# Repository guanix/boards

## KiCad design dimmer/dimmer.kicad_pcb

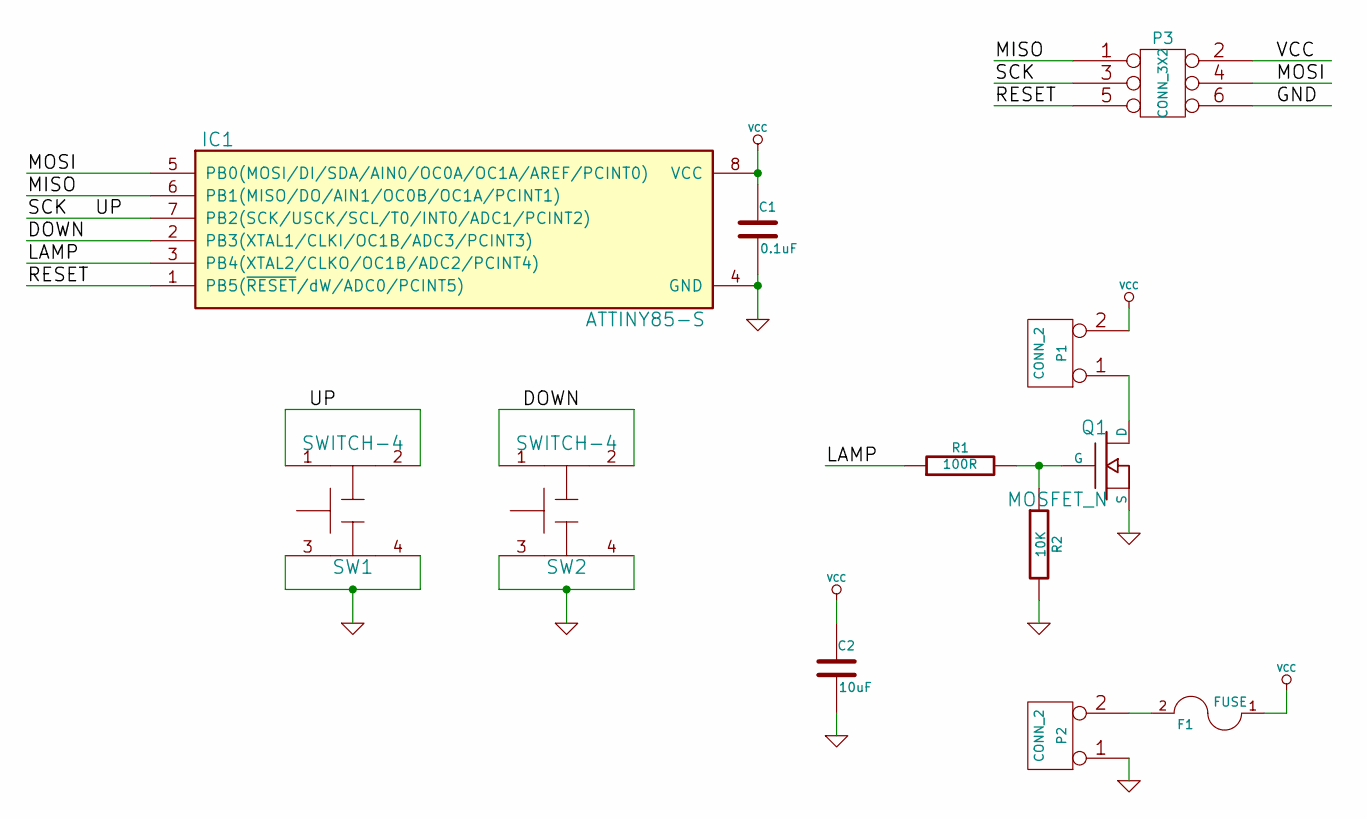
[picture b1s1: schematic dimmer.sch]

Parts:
C1: 0.1uF
C2: 10uF
F1: FUSE
IC1: ATTINY85-S; SO8-200
P1, P2: CONN_2
P3: CONN_3X2
Q1: MOSFET_N
R1: 100R
R2: 10K
SW1, SW2: SWITCH-4

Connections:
/DOWN: IC1.2 (PB3(XTAL1/CLKI/OC1B/ADC3/PCINT3)), SW2.1, SW2.2
/LAMP: IC1.3 (PB4(XTAL2/CLKO/OC1B/ADC2/PCINT4)), R1.1
/MISO: IC1.6 (PB1(MISO/DO/AIN1/OC0B/OC1A/PCINT1)), P3.1
/MOSI: IC1.5 (PB0(MOSI/DI/SDA/AIN0/OC0A/OC1A/AREF/PCI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), P3.4
/RESET: IC1.1 (PB5(~RESET~/dW/ADC0/PCINT5)), P3.5
/SCK: IC1.7 (PB2(SCK/USCK/SCL/T0/INT0/ADC1/PCINT2)), P3.3, SW1.1, SW1.2
GND: C1.2, C2.2, IC1.4 (GND), P2.1, P3.6, Q1.S, R2.2, SW1.3, SW1.4, SW2.3, SW2.4
unnamed: F1.2, P2.2 (PM)
unnamed: P1.1, Q1.D
unnamed: Q1.G, R1.2, R2.1
VCC: C1.1, C2.1, F1.1, IC1.8 (VCC), P1.2 (PM), P3.2

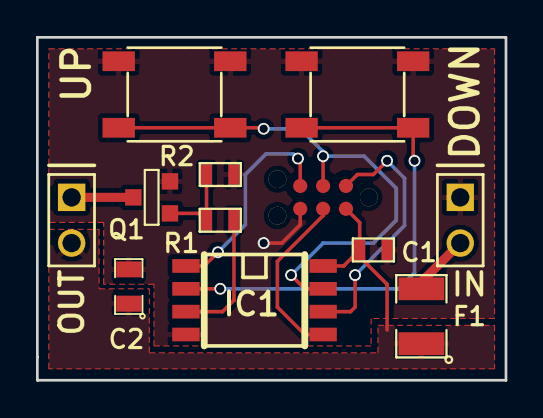
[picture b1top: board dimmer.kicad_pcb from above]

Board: 2 copper layers, 26.0 x 19.0 mm, 12 parts (0 on the bottom side), 11 nets.

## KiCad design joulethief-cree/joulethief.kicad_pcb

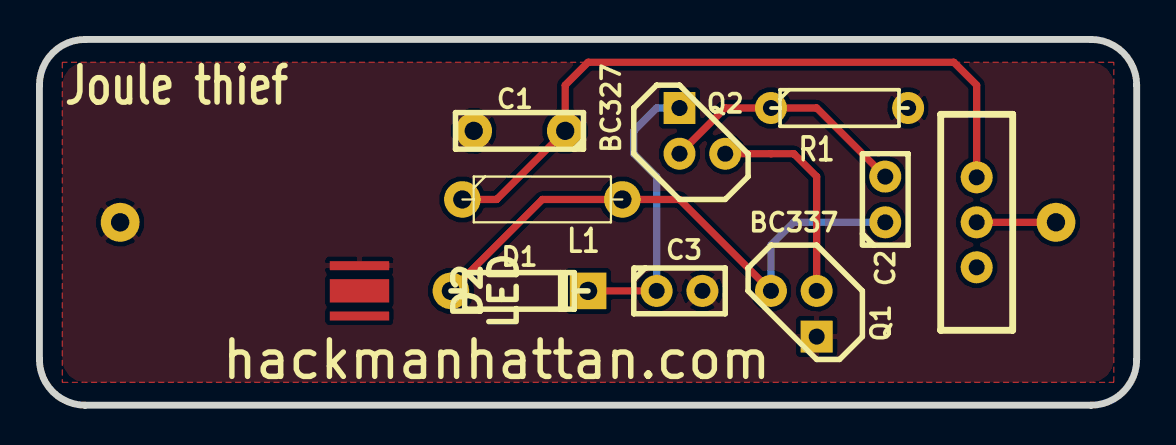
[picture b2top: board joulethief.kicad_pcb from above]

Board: 2 copper layers, 61.0 x 20.3 mm, 11 parts (1 on the bottom side), 7 nets.

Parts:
BT1: BATTERY; BATTERY-AA
C1: 10uF; C2
C2: 150pF; C1
C3: 100nF; C1
D1: 1N4148; D3
D2: LED; CREE-XPC-LED
L1: 22uH; R3-5
Q1: BC337; TO92
Q2: BC327; TO92
R1: 100K; R3
SW1: SWITCH_INV; SWITCH-SPDT-EG1218

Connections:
GND: BT1.2, C1.2, C3.2, D2.2, Q1.1, R1.2
unnamed: BT1.1, SW1.2
unnamed: C2.1, D1.1, D2.1, L1.2, Q1.3
unnamed: Q1.2, Q2.3
unnamed: C1.1, L1.1, SW1.3
unnamed: C3.1, D1.2, Q2.1
unnamed: C2.2, Q2.2, R1.1

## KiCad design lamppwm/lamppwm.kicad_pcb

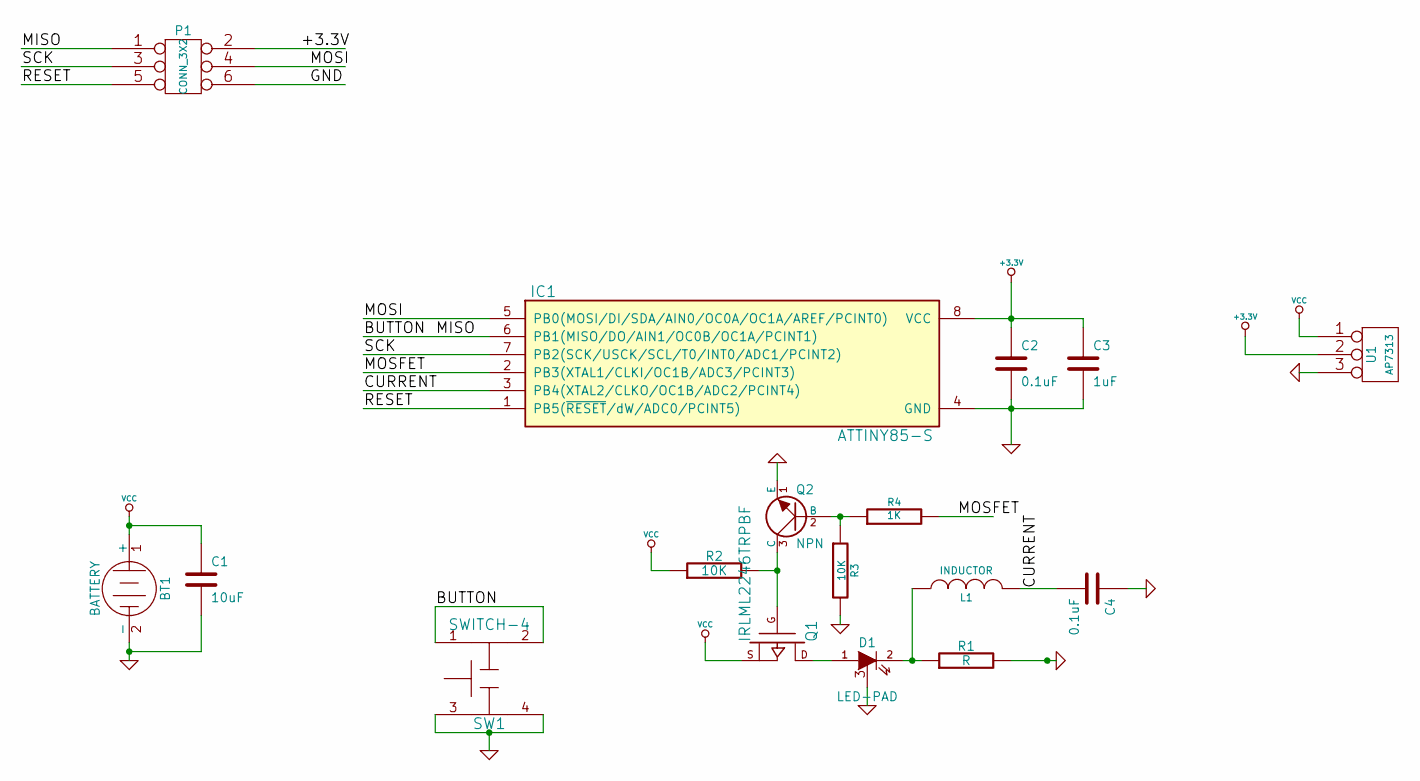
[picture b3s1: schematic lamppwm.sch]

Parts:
BT1: BATTERY
C1: 10uF
C2, C4: 0.1uF
C3: 1uF
D1: LED-PAD
IC1: ATTINY85-S; SO8-200
L1: INDUCTOR
P1: CONN_3X2
Q1: IRLML2246TRPBF
Q2: NPN
R1: R
R2: 10K
R3: 10K
R4: 1K
SW1: SWITCH-4
U1: AP7313

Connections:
+3.3V: C2.1, C3.1, IC1.8 (VCC), P1.2, U1.2 (PM)
/BUTTON: IC1.6 (PB1(MISO/DO/AIN1/OC0B/OC1A/PCINT1)), P1.1, SW1.1, SW1.2
/CURRENT: C4.2, IC1.3 (PB4(XTAL2/CLKO/OC1B/ADC2/PCINT4)), L1.2
/MOSFET: IC1.2 (PB3(XTAL1/CLKI/OC1B/ADC3/PCINT3)), R4.2
/MOSI: IC1.5 (PB0(MOSI/DI/SDA/AIN0/OC0A/OC1A/AREF/PCI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), P1.4
/RESET: IC1.1 (PB5(~RESET~/dW/ADC0/PCINT5)), P1.5
/SCK: IC1.7 (PB2(SCK/USCK/SCL/T0/INT0/ADC1/PCINT2)), P1.3
GND: BT1.2 (-), C1.2, C2.2, C3.2, C4.1, D1.3 (PAD), IC1.4 (GND), P1.6, Q2.1 (E), R1.2, R3.2, SW1.3, SW1.4, U1.3
unnamed: D1.1 (A), Q1.D
unnamed: Q2.2 (B), R3.1, R4.1
unnamed: Q1.G, Q2.3 (C), R2.2
unnamed: D1.2 (K), L1.1, R1.1
VCC: BT1.1 (+), C1.1, Q1.S, R2.1, U1.1

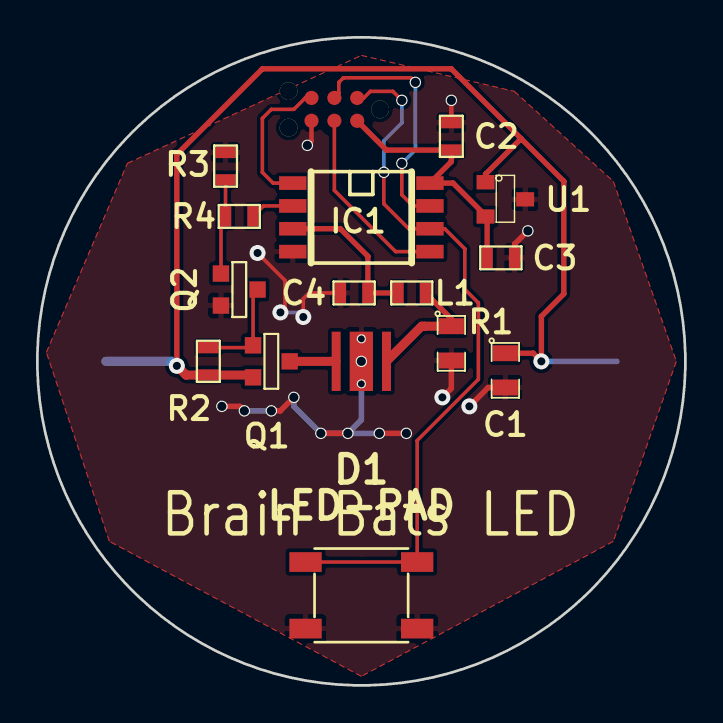
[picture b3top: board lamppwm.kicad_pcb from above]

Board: 2 copper layers, 36.0 x 36.0 mm, 17 parts (1 on the bottom side), 13 nets.

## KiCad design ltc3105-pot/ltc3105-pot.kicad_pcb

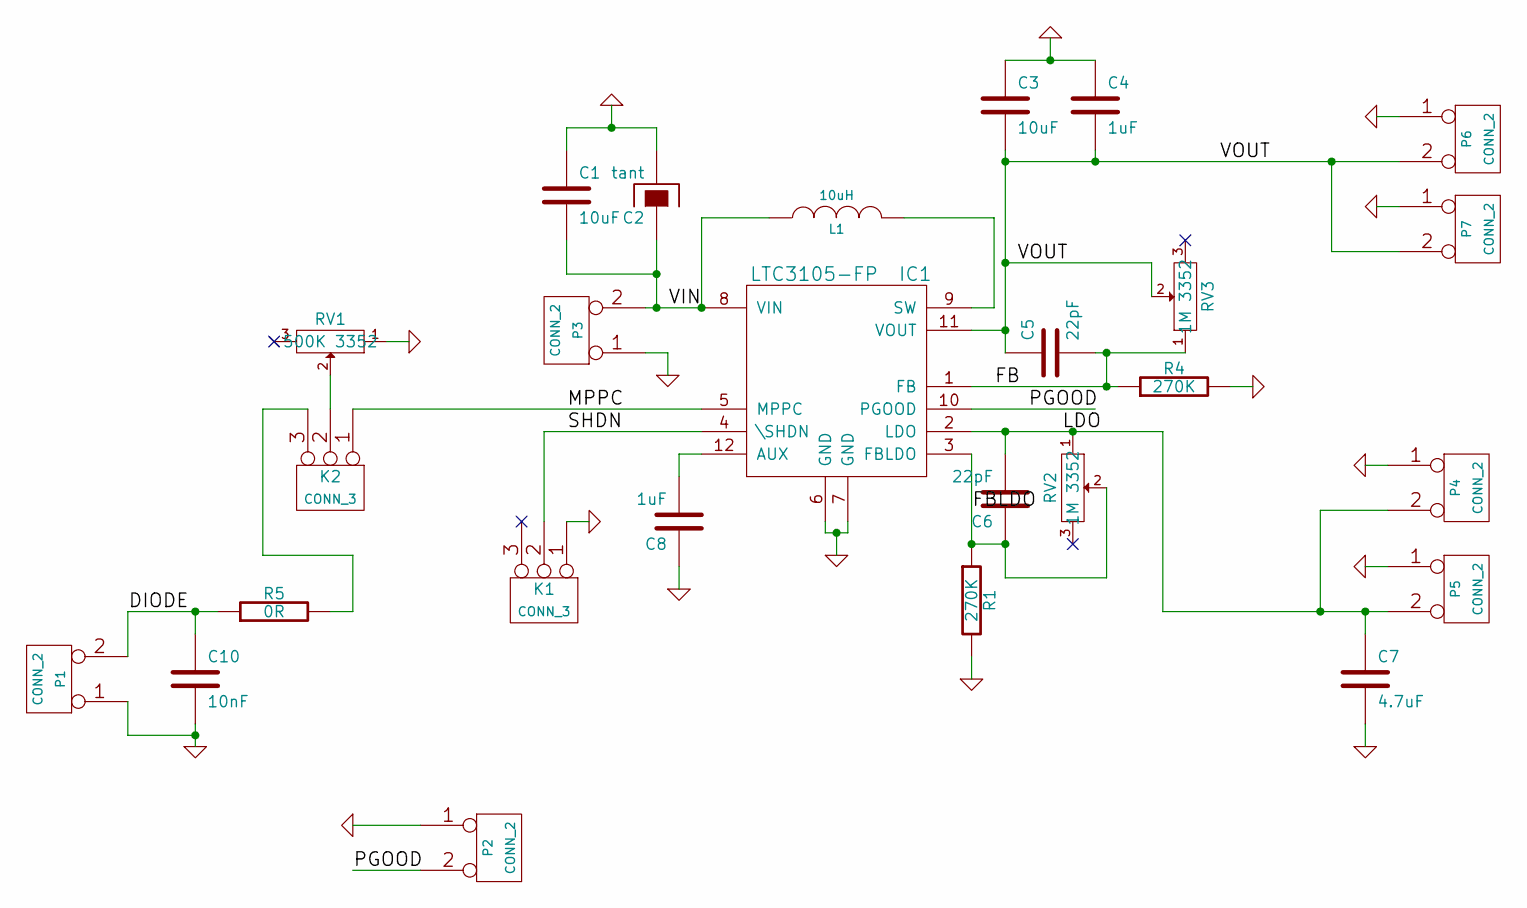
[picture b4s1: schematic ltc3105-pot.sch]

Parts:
C1, C3: 10uF
C2: tant
C4, C8: 1uF
C5, C6: 22pF
C7: 4.7uF
C10: 10nF
IC1: LTC3105-FP
K1, K2: CONN_3
L1: 10uH
P1, P2, P3, P4, P5, P6, P7: CONN_2
R1, R4: 270K
R5: 0R
RV1: 500K 3352
RV2, RV3: 1M 3352

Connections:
/DIODE: C10.1, P1.2 (PM), R5.1
/FB: C5.2, IC1.1 (FB), R4.1, RV3.1
/FBLDO: C6.1, IC1.3 (FBLDO), R1.1, RV2.2
/LDO: C6.2, C7.1, IC1.2 (LDO), P4.2 (PM), P5.2 (PM), RV2.1
/MPPC: IC1.5 (MPPC), K2.1
/PGOOD: IC1.10 (PGOOD), P2.2 (PM)
/SHDN: IC1.4 (\SHDN), K1.2 (PM)
/VIN: C1.2, C2.1, IC1.8 (VIN), L1.1, P3.2 (PM)
/VOUT: C3.2, C4.2, C5.1, IC1.11 (VOUT), P6.2 (PM), P7.2 (PM), RV3.2
GND: C1.1, C2.2, C3.1, C4.1, C7.2, C8.1, C10.2, IC1.6 (GND), IC1.7 (GND), K1.1, P1.1, P2.1, P3.1, P4.1, P5.1, P6.1, P7.1, R1.2, R4.2, RV1.1
unnamed: K2.2 (PM), RV1.2
unnamed: K2.3, R5.2
unnamed: IC1.9 (SW), L1.2
unnamed: C8.2, IC1.12 (AUX)

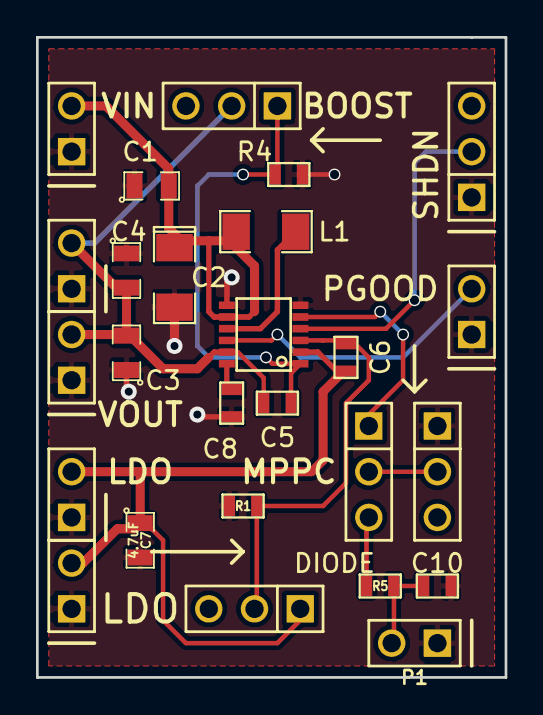
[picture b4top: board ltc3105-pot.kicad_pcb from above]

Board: 2 copper layers, 26.0 x 35.6 mm, 26 parts (0 on the bottom side), 14 nets.

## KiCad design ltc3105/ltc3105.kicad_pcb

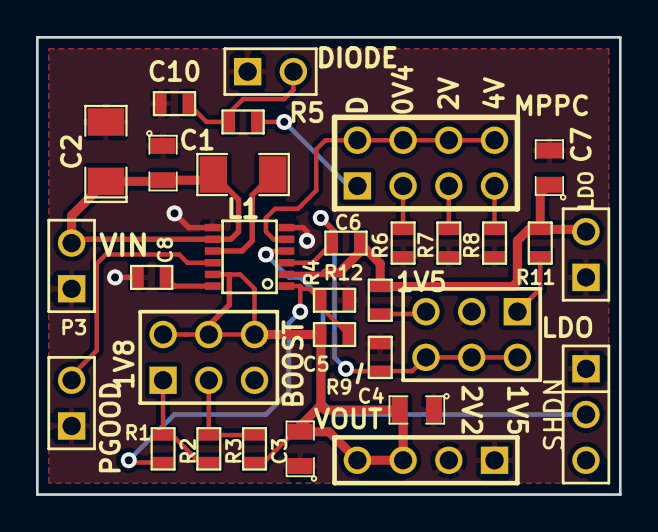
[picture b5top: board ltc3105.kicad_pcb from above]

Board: 2 copper layers, 32.4 x 25.4 mm, 31 parts (0 on the bottom side), 20 nets.

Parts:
BOOST: CONN_3X2; pin_array_3x2
C1, C3: 10uF; SM0805
C2: tant; SM1206POL
C4: 1uF; SM0805
C5, C6: 33pF; SM0603
C7: 4.7uF; SM0805
C8: 1uF; SM0603
C10: 10nF; SM0603
IC1: LTC3105-FP; MSOP-12
L1: 10uH; SM1206
LDO: CONN_3X2; pin_array_3x2
LDO#2: CONN_2; PIN_ARRAY_2X1
MPPC: CONN_4X2; pin_array_4x2
P1, P3: CONN_2; PIN_ARRAY_2X1
PGOOD: CONN_2; PIN_ARRAY_2X1
R1: 392K; SM0603
R2: 750K; SM0603
R3: 845K; SM0603
R4: 499K; SM0603
R5: 0R; SM0603
R6: 40K2; SM0603
R7: 200K; SM0603
R8: 402K; SM0603
R9: 549K; SM0603
R11: 274K; SM0603
R12: 1M1; SM0603
SHDN: CONN_3; PIN_ARRAY_3X1
VOUT: CONN_4; PIN_ARRAY_4x1

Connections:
/DIODE: C10.1, P1.2, R5.1
/FB: C5.2, IC1.1, R1.1, R4.1
/LDO: C6.2, C7.1, IC1.2, LDO#2.2, R11.2, R12.2
/MPPC: IC1.5, MPPC.2, MPPC.4, MPPC.6, MPPC.8
/PGOOD: IC1.10, PGOOD.2
/SHDN: IC1.4, SHDN.2
/VIN: C1.2, C2.1, IC1.8, L1.1, P3.2
/VOUT: BOOST.2, BOOST.4, BOOST.6, C3.2, C4.2, C5.1, IC1.11, R3.2, VOUT.3, VOUT.4
GND: C1.1, C2.2, C3.1, C4.1, C7.2, C8.1, C10.2, IC1.6, IC1.7, LDO.3, LDO#2.1, P1.1, P3.1, PGOOD.1, R4.2, R6.2, R7.2, R8.2, R9.1, SHDN.1, VOUT.1, VOUT.2
unnamed: BOOST.1, R1.2, R2.1
unnamed: BOOST.3, R2.2, R3.1
unnamed: MPPC.1, R5.2
unnamed: MPPC.7, R8.1
unnamed: MPPC.5, R7.1
unnamed: MPPC.3, R6.1
unnamed: LDO.5, R12.1
unnamed: LDO.1, R11.1
unnamed: C6.1, IC1.3, LDO.2, LDO.4, LDO.6, R9.2
unnamed: IC1.9, L1.2
unnamed: C8.2, IC1.12

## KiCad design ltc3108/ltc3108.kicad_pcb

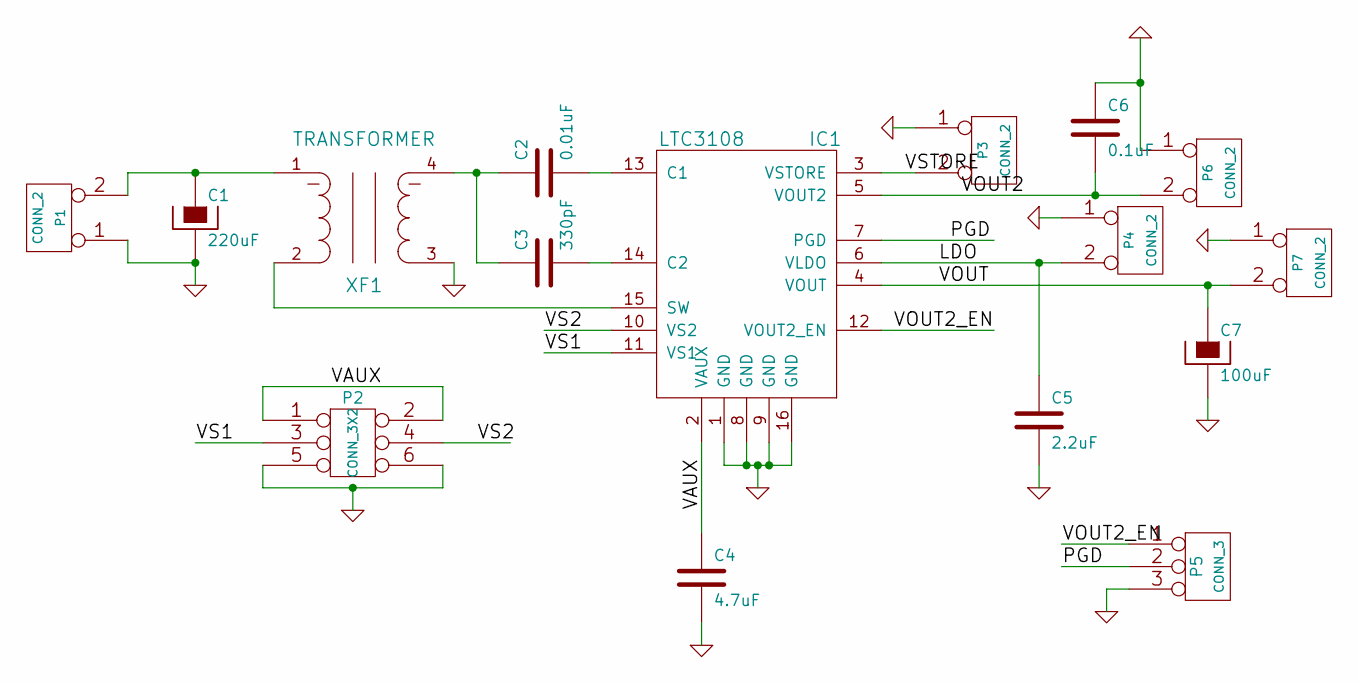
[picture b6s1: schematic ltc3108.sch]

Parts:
C1: 220uF
C2: 0.01uF
C3: 330pF
C4: 4.7uF
C5: 2.2uF
C6: 0.1uF
C7: 100uF
IC1: LTC3108
P1, P3, P4, P6, P7: CONN_2
P2: CONN_3X2
P5: CONN_3
XF1: TRANSFORMER

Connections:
/LDO: C5.1, IC1.6 (VLDO), P4.2 (PM)
/PGD: IC1.7 (PGD), P5.2 (PM)
/VAUX: C4.1, IC1.2 (VAUX), P2.1, P2.2
/VOUT: C7.1, IC1.4 (VOUT), P7.2 (PM)
/VOUT2: C6.2, IC1.5 (VOUT2), P6.2 (PM)
/VOUT2_EN: IC1.12 (VOUT2_EN), P5.1
/VS1: IC1.11 (VS1), P2.3
/VS2: IC1.10 (VS2), P2.4
/VSTORE: IC1.3 (VSTORE), P3.2 (PM)
GND: C1.2, C4.2, C5.2, C6.1, C7.2, IC1.1 (GND), IC1.8 (GND), IC1.9 (GND), IC1.16 (GND), P1.1, P2.5, P2.6, P3.1, P4.1, P5.3, P6.1, P7.1, XF1.3
unnamed: IC1.15 (SW), XF1.2
unnamed: C2.2, IC1.13 (C1)
unnamed: C2.1, C3.1, XF1.4
unnamed: C3.2, IC1.14 (C2)
unnamed: C1.1, P1.2 (PM), XF1.1

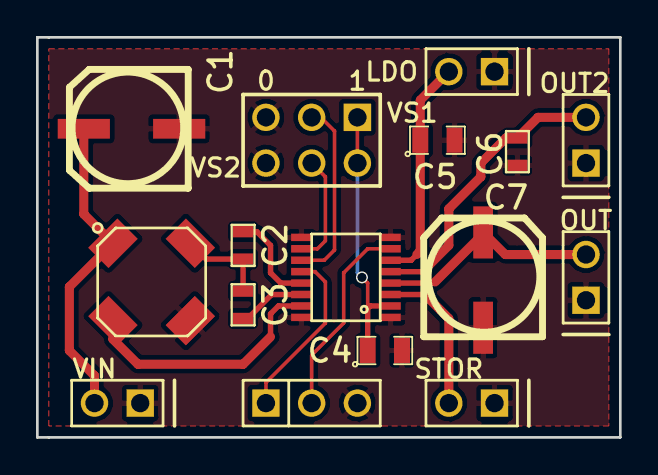
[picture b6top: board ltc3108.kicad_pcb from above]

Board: 2 copper layers, 32.4 x 22.2 mm, 16 parts (0 on the bottom side), 15 nets.
